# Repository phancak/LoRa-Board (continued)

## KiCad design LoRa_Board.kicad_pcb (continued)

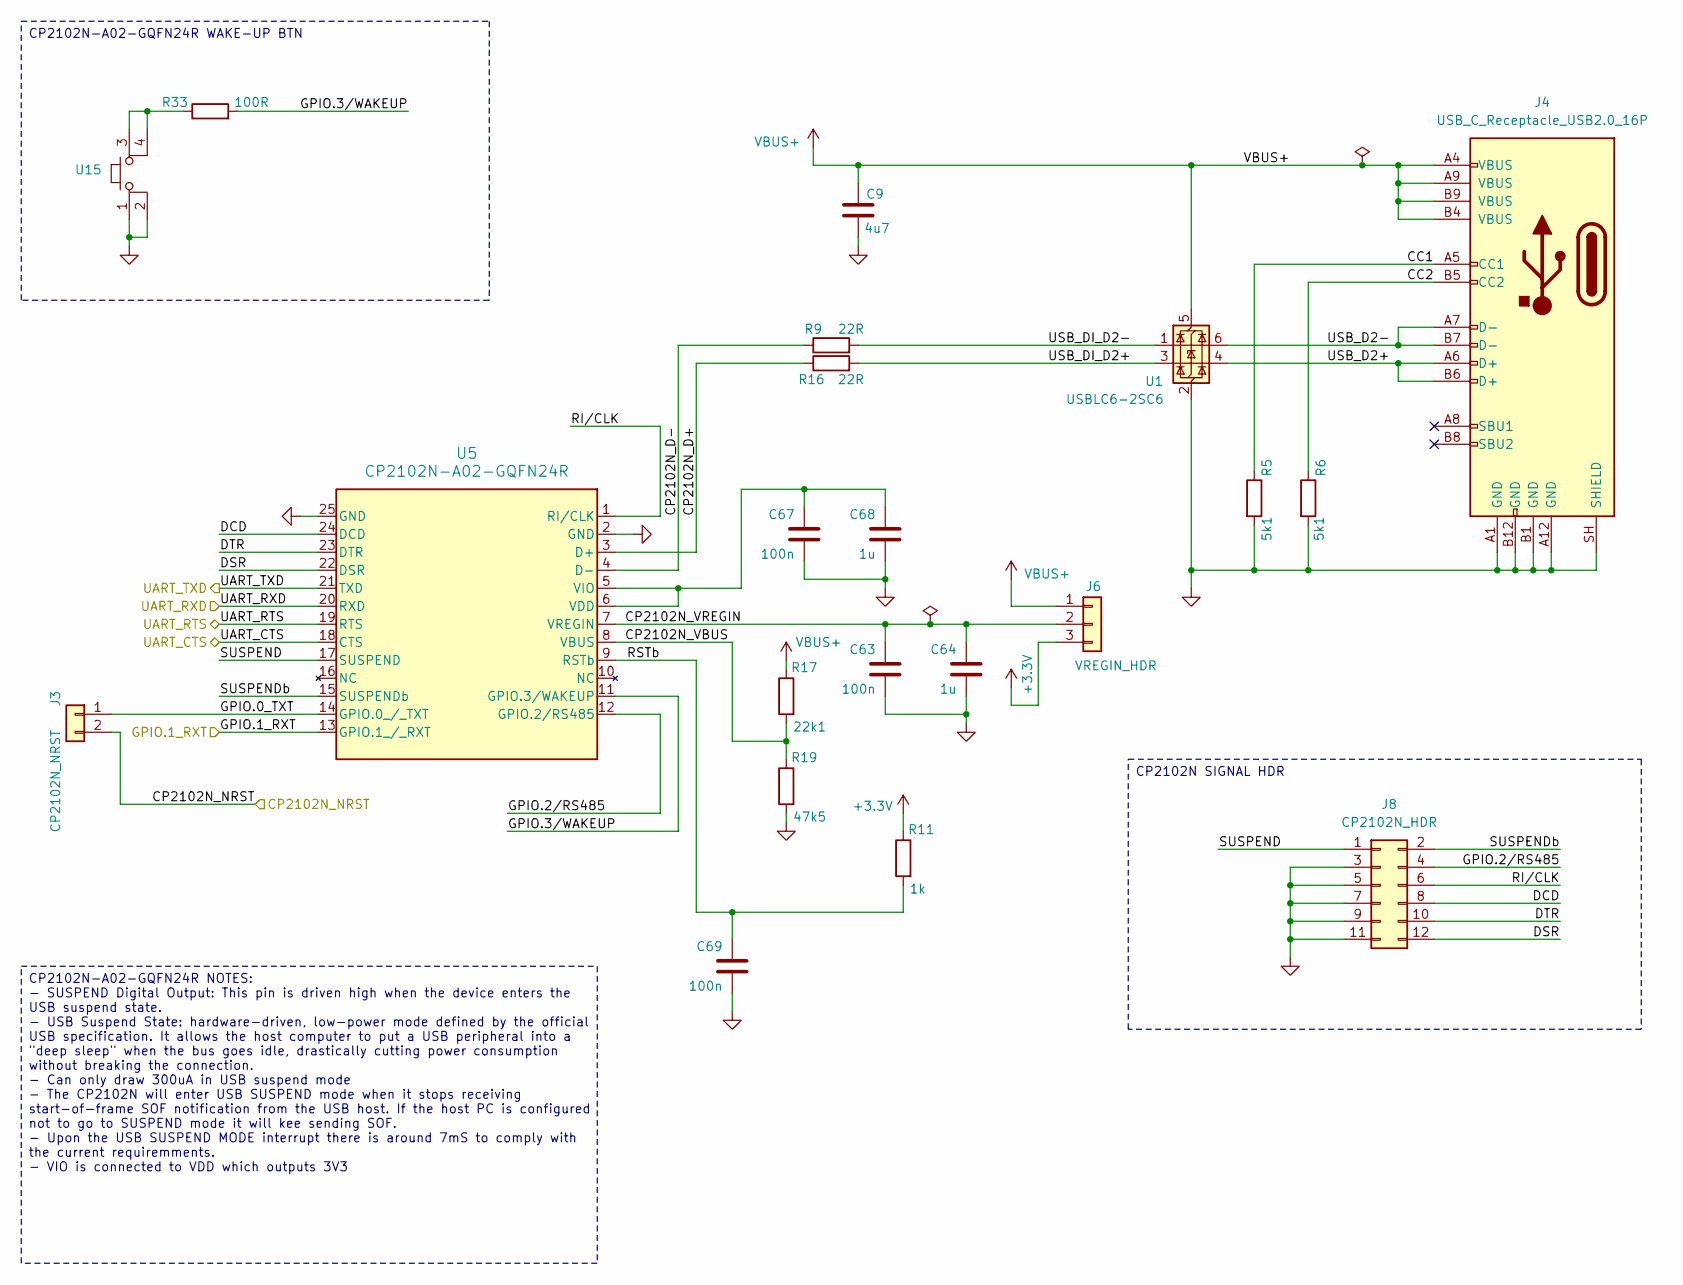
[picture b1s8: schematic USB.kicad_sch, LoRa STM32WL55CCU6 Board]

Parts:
C9: 4u7; C_0805_2012Metric
C63, C69: 100n; C_0603_1608Metric
C64: 1u; C_0603_1608Metric
C67: 100n; C_0805_2012Metric
C68: 1u; C_0805_2012Metric
J3: CP2102N_NRST; PinHeader_1x02_P2.54mm_Vertical
J4: USB_C_Receptacle_USB2.0_16P; USB_C_Receptacle_HRO_TYPE-C-31-M-12
J6: VREGIN_HDR; PinHeader_1x03_P2.54mm_Vertical
J8: CP2102N_HDR; PinHeader_2x06_P2.54mm_Horizontal
R5, R6: 5k1; R_0603_1608Metric
R9, R16: 22R; R_0603_1608Metric
R11: 1k; R_0603_1608Metric
R17: 22k1; R_0603_1608Metric
R19: 47k5; R_0603_1608Metric
R33: 100R; R_0805_2012Metric
U1: USBLC6-2SC6; SOT-23-6
U5: CP2102N-A02-GQFN24R; CP2102N_A02_GQFN24R_QFN24_SIL
U15: Button_SKSCLCE010

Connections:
+3.3V: J6.3, R11.1; also elsewhere on the board
/Power_Management/BFR_RST: J3.2; also elsewhere on the board
/STM32WL55CCU6_GPIO/BOOT0_EXTCTR: U5.13 (GPIO.1_/_RXT); also elsewhere on the board
/STM32WL55CCU6_GPIO/PA2_USART2_TX: U5.20 (RXD); also elsewhere on the board
/STM32WL55CCU6_GPIO/PA3_USART2_RX: U5.21 (TXD); also elsewhere on the board
/USB/CC1: J4.A5 (CC1), R5.1
/USB/CC2: J4.B5 (CC2), R6.1
/USB/CP2102N_D+: R16.1, U5.3 (D+)
/USB/CP2102N_D-: R9.1, U5.4 (D-)
/USB/CP2102N_VBUS: R17.2, R19.1, U5.8 (VBUS)
/USB/CP2102N_VREGIN: C63.1, C64.1, J6.2, U5.7 (VREGIN)
/USB/DCD: J8.8, U5.24 (DCD)
/USB/DSR: J8.12, U5.22 (DSR)
/USB/DTR: J8.10, U5.23 (DTR)
/USB/GPIO.0_TXT: J3.1, U5.14 (GPIO.0_/_TXT)
/USB/GPIO.2/RS485: J8.4, U5.12 (GPIO.2/RS485)
/USB/GPIO.3/WAKEUP: R33.2, U5.11 (GPIO.3/WAKEUP)
/USB/RI/CLK: J8.6, U5.1 (RI/CLK)
/USB/RSTb: C69.1, R11.2, U5.9 (RSTb)
/USB/SUSPEND: J8.1, U5.17 (SUSPEND)
/USB/SUSPENDb: J8.2, U5.15 (SUSPENDb)
/USB/UART_CTS: U5.18 (CTS)
/USB/UART_RTS: U5.19 (RTS)
/USB/USB_D2+: J4.A6 (D+), J4.B6 (D+), U1.4 (I/O2)
/USB/USB_D2-: J4.A7 (D-), J4.B7 (D-), U1.6 (I/O1)
/USB/USB_DI_D2+: R16.2, U1.3 (I/O2)
/USB/USB_DI_D2-: R9.2, U1.1 (I/O1)
GND: C9.2, C63.2, C64.2, C67.2, C68.2, C69.2, J4.A1 (GND), J4.A12 (GND), J4.B1 (GND), J4.B12 (GND), J4.SH (SHIELD), J8.3, J8.5, J8.7, J8.9, J8.11, R5.2, R6.2, R19.2, U1.2 (GND), U5.2 (GND), U5.25 (GND), U15.1, U15.2; also elsewhere on the board
unnamed: R33.1, U15.3, U15.4
unnamed: C67.1, C68.1, U5.5 (VIO), U5.6 (VDD)
VBUS+: C9.1, J4.A4 (VBUS), J4.A9 (VBUS), J4.B4 (VBUS), J4.B9 (VBUS), J6.1, R17.1, U1.5 (VBUS); also elsewhere on the board

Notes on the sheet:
CP2102N-A02-GQFN24R WAKE-UP BTN
CP2102N-A02-GQFN24R NOTES: - SUSPEND Digital Output: This pin is driven high when the device enters the USB suspend state. - USB Suspend State: hardware-driven, low-power mode defined by the official USB specification. It allows the host computer to put a USB peripheral into a "deep sleep" when the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
CP2102N SIGNAL HDR

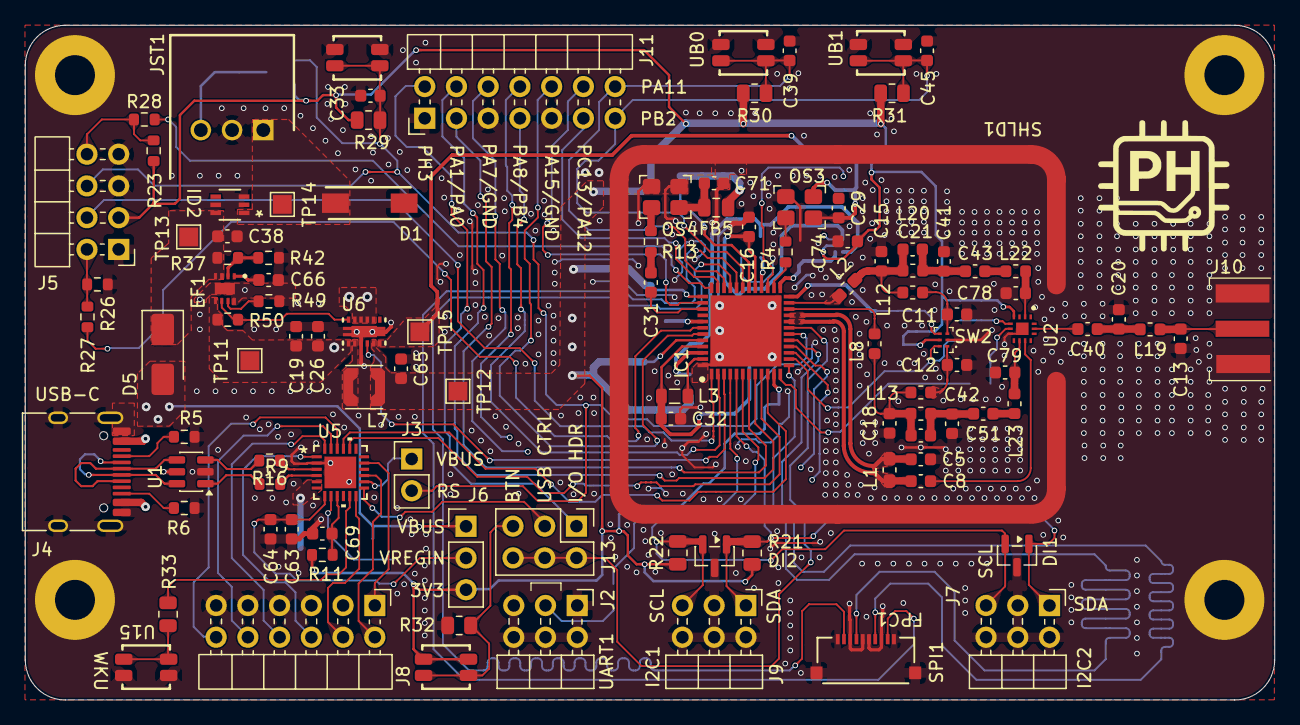
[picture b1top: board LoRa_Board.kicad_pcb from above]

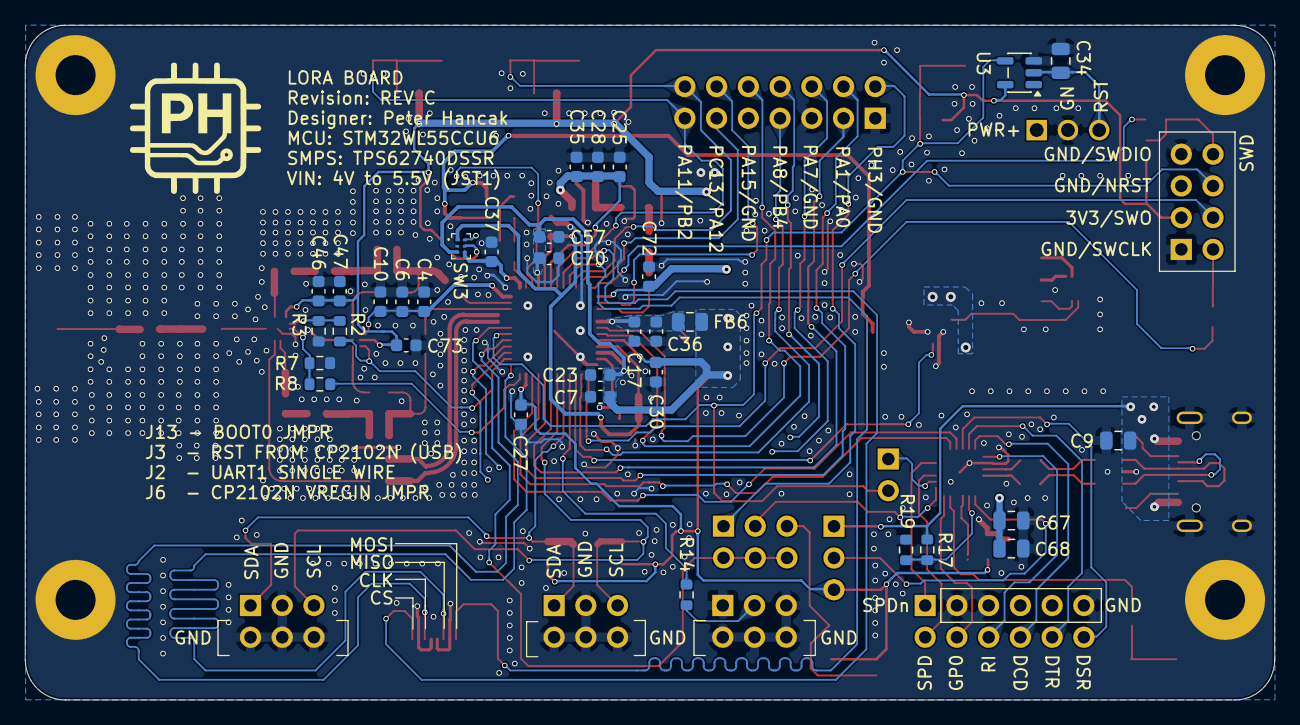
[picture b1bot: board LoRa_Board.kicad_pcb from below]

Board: 4 copper layers, 100.0 x 54.0 mm, 144 parts (33 on the bottom side), 101 nets.

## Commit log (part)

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2026-03-17 Update Readme file
2026-03-17 Update file name
2026-06-24 Schematics Update
